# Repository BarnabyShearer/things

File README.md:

[//]: # (Autogenerated by https://github.com/BarnabyShearer/meta)

# things

Designs for lasercutting, 3D printing, milling etc.

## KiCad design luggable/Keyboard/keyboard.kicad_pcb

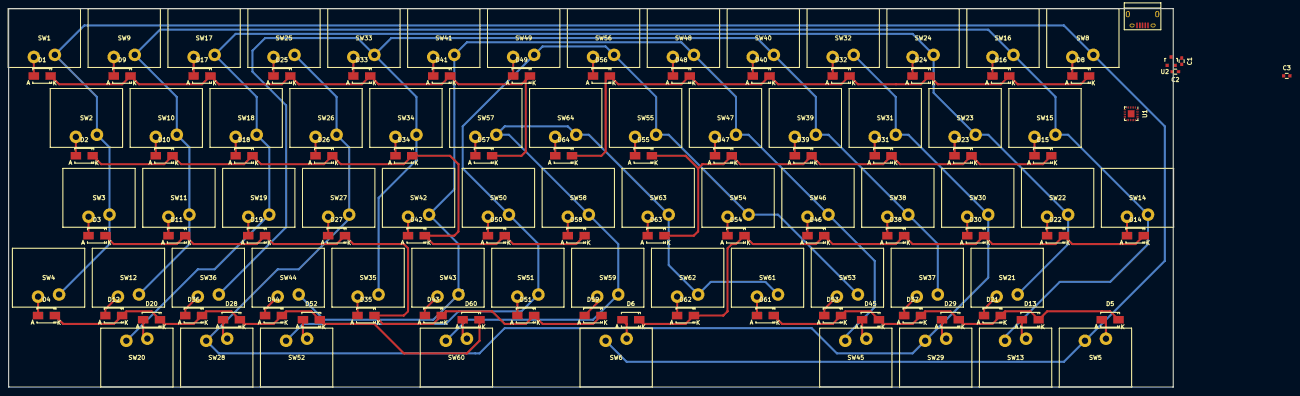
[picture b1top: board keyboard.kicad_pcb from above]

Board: 2 copper layers, 277.0 x 90.0 mm, 132 parts (0 on the bottom side), 84 nets.

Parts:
C1, C2, C3: C; C_0603
CON1: USB-MICRO-B; USB_Micro-B
D1, D2, D3, D4, D5, D6, D8, D9, D10, D11, D12, D13, D14, D15, D16, D17, D18, D19, D20, D21, D22, D23, D24, D25, D26, D27, D28, D29, D30, D31, D32, D33, D34, D35, D36, D37, D38, D39, D40, D41, D42, D43, D44, D45, D46, D47, D48, D49, D50, D51, D52, D53, D54, D55, D56, D57, D58, D59, D60, D61, D62, D63, D64: DIODE; Diode-SMA_Standard
SW1, SW2, SW3, SW4, SW5, SW6, SW8, SW9, SW10, SW11, SW12, SW13, SW14, SW15, SW16, SW17, SW18, SW19, SW20, SW21, SW22, SW23, SW24, SW25, SW26, SW27, SW28, SW29, SW30, SW31, SW32, SW33, SW34, SW35, SW36, SW37, SW38, SW39, SW40, SW41, SW42, SW43, SW44, SW45, SW46, SW47, SW48, SW49, SW50, SW51, SW52, SW53, SW54, SW55, SW56, SW57, SW58, SW59, SW60, SW61, SW62, SW63, SW64: SW_PUSH_SMALL; SW_Matias_Quiet
U1: ADP5589; QFN-24-1EP_3x3mm_Pitch0.4mm
U2: APE8865N-33-HF-3; SOT-23

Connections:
+3V3: C1.1, C3.1, U1.17, U1.18, U2.2
GND: C1.2, C2.2, C3.2, CON1.5, U1.25, U2.1
unnamed: C2.1, CON1.1, U2.3
unnamed: CON1.2, U1.23
unnamed: CON1.3, U1.22
unnamed: D1.1, SW1.2
unnamed: D1.2, D9.2, D17.2, D25.2, D33.2, D41.2, D49.2, D57.2, U1.11
unnamed: D2.1, SW2.2
unnamed: D3.1, SW3.2
unnamed: D4.1, SW4.2
unnamed: D5.1, SW5.2
unnamed: D6.1, SW6.2
unnamed: D8.1, SW8.2
unnamed: D9.1, SW9.2
unnamed: D10.1, SW10.2
unnamed: D2.2, D10.2, D18.2, D26.2, D34.2, D42.2, D50.2, D58.2, U1.12
unnamed: D11.1, SW11.2
unnamed: D3.2, D11.2, D19.2, D27.2, D35.2, D43.2, D51.2, D59.2, U1.13
unnamed: D12.1, SW12.2
unnamed: D4.2, D12.2, D20.2, D28.2, D36.2, D44.2, D52.2, D60.2, U1.14
unnamed: D13.1, SW13.2
unnamed: D5.2, D13.2, D21.2, D29.2, D37.2, D45.2, D53.2, D61.2, U1.15
unnamed: D14.1, SW14.2
unnamed: D6.2, D14.2, D22.2, D30.2, D38.2, D46.2, D54.2, D62.2, U1.9
unnamed: D15.1, SW15.2
unnamed: D15.2, D23.2, D31.2, D39.2, D47.2, D55.2, D63.2, U1.10
unnamed: D16.1, SW16.2
unnamed: D8.2, D16.2, D24.2, D32.2, D40.2, D48.2, D56.2, D64.2, U1.16
unnamed: D17.1, SW17.2
unnamed: D18.1, SW18.2
unnamed: D19.1, SW19.2
unnamed: D20.1, SW20.2
unnamed: D21.1, SW21.2
unnamed: D22.1, SW22.2
unnamed: D23.1, SW23.2
unnamed: D24.1, SW24.2
unnamed: D25.1, SW25.2
unnamed: D26.1, SW26.2
unnamed: D27.1, SW27.2
unnamed: D28.1, SW28.2
unnamed: D29.1, SW29.2
unnamed: D30.1, SW30.2
unnamed: D31.1, SW31.2
unnamed: D32.1, SW32.2
unnamed: D33.1, SW33.2
unnamed: D34.1, SW34.2
unnamed: D35.1, SW35.2
unnamed: D36.1, SW36.2
unnamed: D37.1, SW37.2
unnamed: D38.1, SW38.2
unnamed: D39.1, SW39.2
unnamed: D40.1, SW40.2
unnamed: D41.1, SW41.2
unnamed: D42.1, SW42.2
unnamed: D43.1, SW43.2
unnamed: D44.1, SW44.2
unnamed: D45.1, SW45.2
unnamed: D46.1, SW46.2
unnamed: D47.1, SW47.2
unnamed: D48.1, SW48.2
unnamed: D49.1, SW49.2
unnamed: D50.1, SW50.2
unnamed: D51.1, SW51.2
unnamed: D52.1, SW52.2
unnamed: D53.1, SW53.2
unnamed: D54.1, SW54.2
unnamed: D55.1, SW55.2
unnamed: D56.1, SW56.2
unnamed: D57.1, SW57.2
unnamed: D58.1, SW58.2
unnamed: D59.1, SW59.2
unnamed: D60.1, SW60.2
unnamed: D61.1, SW61.2
unnamed: D62.1, SW62.2
unnamed: D63.1, SW63.2
unnamed: D64.1, SW64.2
unnamed: SW1.1, SW2.1, SW3.1, SW4.1, SW5.1, SW6.1, SW8.1, U1.1
unnamed: SW9.1, SW10.1, SW11.1, SW12.1, SW13.1, SW14.1, SW15.1, SW16.1, U1.2
unnamed: SW17.1, SW18.1, SW19.1, SW20.1, SW21.1, SW22.1, SW23.1, SW24.1, U1.3
unnamed: SW25.1, SW26.1, SW27.1, SW28.1, SW29.1, SW30.1, SW31.1, SW32.1, U1.5
unnamed: SW33.1, SW34.1, SW35.1, SW36.1, SW37.1, SW38.1, SW39.1, SW40.1, U1.4
unnamed: SW41.1, SW42.1, SW43.1, SW44.1, SW45.1, SW46.1, SW47.1, SW48.1, U1.6
unnamed: SW49.1, SW50.1, SW51.1, SW52.1, SW53.1, SW54.1, SW55.1, SW56.1, U1.7
unnamed: SW57.1, SW58.1, SW59.1, SW60.1, SW61.1, SW62.1, SW63.1, SW64.1, U1.8

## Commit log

2012-05-20 first things
2012-05-22 v2 mounts
2012-06-08 try bushings
2012-06-16 hotend tweeks
2012-06-22 MF70
2012-06-22 tinkering
2012-06-27 Bowden Extruder
2012-08-01 simplify sizing
2012-08-01 Clamping the braid proved less successful with time, the tried and trusted nut approch wins out
2012-08-01 better fan position
2012-08-01 Keeps the filament strait in the extruder, probably not normaly needed but really helps a bowden setup
2012-08-01 Improves frame rigidity
2012-08-01 Cleanup
2012-10-29 Idea
2012-10-29 Faster cutting
2012-10-29 Some hand optimziations for my mill
2012-10-29 misc
2012-11-18 knitting
2012-11-29 extruder improvements
2012-11-29 useful
2012-12-18 1st try
2012-12-18 Rearange for HackHD
2012-12-18 2d output
2012-12-18 oops
2012-12-31 final tweeks
2013-01-09 eyepatch
2013-01-22 seal
2013-02-06 first try
2013-03-15 links
2013-07-30 init
2013-08-17 cut n paste error
2013-08-18 better vid
2013-09-22 better design, not finised
2013-09-25 drill
2013-10-02 missing valve covers
2013-10-02 bump lib
2013-11-30 fix subshell issues
2013-11-30 first prototype made
2013-11-30 Difierential ball screws
2013-12-07 thoughts
2013-12-07 posible ends
2013-12-11 bowdens
2014-07-16 1st build
2014-07-28 tidy
2014-09-15 Laser cut cosplay prop
2014-09-15 ready to cut
2014-12-05 fixes
2014-12-06 plate
2015-02-25 first
2015-03-04 vslot
2015-04-10 last of 1/3 size
2015-04-14 one piece
2016-09-23 move submodule
2016-09-23 preview
2016-10-09 chair base for laser cutter
2016-10-17 Air holes and slight tweek to best fit example chairs
2017-03-18 backup robots' table
2017-06-11 clock
2017-06-13 schematic
2017-11-15 misc lost files
2017-11-15 fix submodule
2017-11-15 extra
2017-11-15 Model railway workshop cradle
2017-11-15 more stuff
2020-06-03 case idea
2021-11-07 Add SECURITY.md
2021-11-12 oven
2021-11-12 mount
2021-11-14 Add README.md
